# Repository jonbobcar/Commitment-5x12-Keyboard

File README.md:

# Lizard Trick 5x12 Keyboard
 A cherry mx compatible 5x12 ortholinear keyboard

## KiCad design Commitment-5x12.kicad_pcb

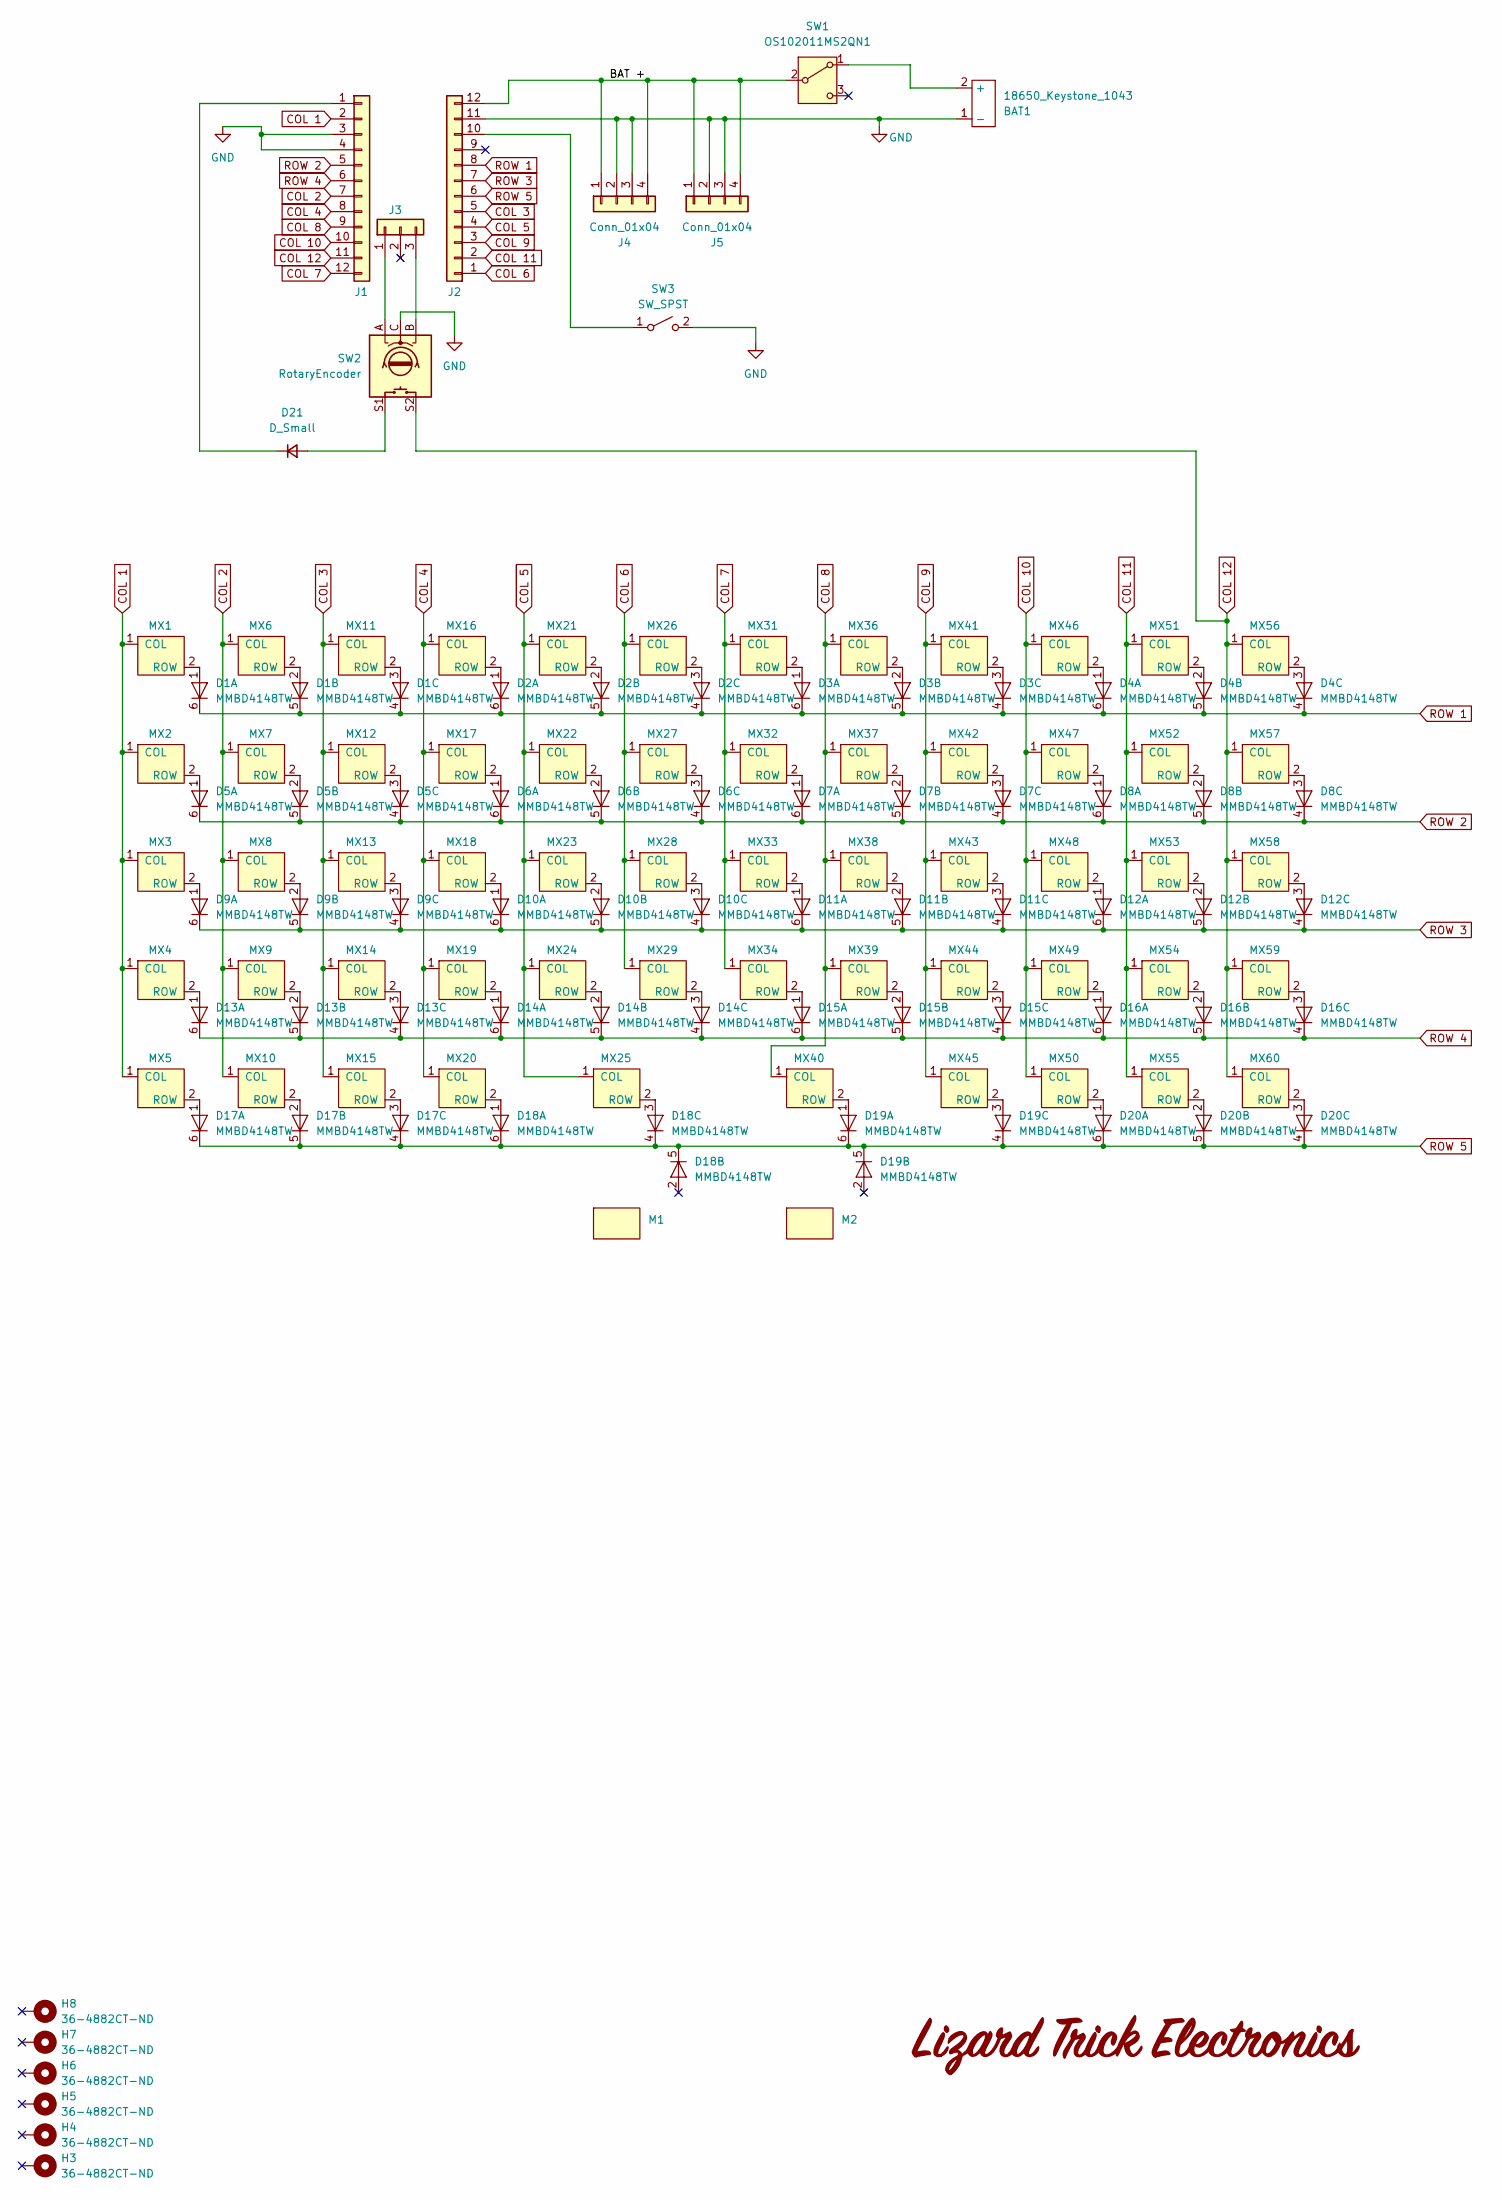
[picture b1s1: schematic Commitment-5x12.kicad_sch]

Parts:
BAT1: 18650_Keystone_1043; Keystone 1043 18650
D1, D2, D3, D4, D5, D6, D7, D8, D9, D10, D11, D12, D13, D14, D15, D16, D17, D18, D19, D20: MMBD4148TW; SOT-363_SC-70-6
D21: D_Small; D_SOD-123
H3, H4, H5, H6, H7, H8: 36-4882CT-ND; Keystone Standoff 4-40 .125
J1, J2: Conn_01x13; PinSocket_1x12_P2.54mm_Vertical
J3: Conn_01x03; PinSocket_1x03_P2.54mm_Vertical
J4, J5: Conn_01x04; MagneticHeader_1x04_P2.54mm_Vertical
M1, M2: MX_2U_Stabilizer_Mount
MX1, MX2, MX3, MX4, MX5, MX6, MX7, MX8, MX9, MX10, MX11, MX12, MX13, MX14, MX15, MX16, MX17, MX18, MX19, MX20, MX21, MX22, MX23, MX24, MX25, MX26, MX27, MX28, MX29, MX31, MX32, MX33, MX34, MX36, MX37, MX38, MX39, MX40, MX41, MX42, MX43, MX44, MX45, MX46, MX47, MX48, MX49, MX50, MX51, MX52, MX53, MX54, MX55, MX56, MX57, MX58, MX59, MX60: MX_Switch; Kailh_MX_Hotswap_Socket
SW1: OS102011MS2QN1; SW_Slide_SPDT_Straight_CK_OS102011MS2Q
SW2: RotaryEncoder; RotaryEncoder_Bourns_PEC11L
SW3: SW_SPST; Omron_B3F-1000

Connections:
/BAT +: J2.12, J4.1, J4.4, J5.1, J5.4, SW1.2 (B)
COL 1: J1.2, MX1.1 (COL), MX2.1 (COL), MX3.1 (COL), MX4.1 (COL), MX5.1 (COL)
COL 2: J1.7, MX6.1 (COL), MX7.1 (COL), MX8.1 (COL), MX9.1 (COL), MX10.1 (COL)
COL 3: J2.5, MX11.1 (COL), MX12.1 (COL), MX13.1 (COL), MX14.1 (COL), MX15.1 (COL)
COL 4: J1.8, MX16.1 (COL), MX17.1 (COL), MX18.1 (COL), MX19.1 (COL), MX20.1 (COL)
COL 5: J2.4, MX21.1 (COL), MX22.1 (COL), MX23.1 (COL), MX24.1 (COL), MX25.1 (COL)
COL 6: J2.1, MX26.1 (COL), MX27.1 (COL), MX28.1 (COL), MX29.1 (COL)
COL 7: J1.12, MX31.1 (COL), MX32.1 (COL), MX33.1 (COL), MX34.1 (COL)
COL 8: J1.9, MX36.1 (COL), MX37.1 (COL), MX38.1 (COL), MX39.1 (COL), MX40.1 (COL)
COL 9: J2.3, MX41.1 (COL), MX42.1 (COL), MX43.1 (COL), MX44.1 (COL), MX45.1 (COL)
COL 10: J1.10, MX46.1 (COL), MX47.1 (COL), MX48.1 (COL), MX49.1 (COL), MX50.1 (COL)
COL 11: J2.2, MX51.1 (COL), MX52.1 (COL), MX53.1 (COL), MX54.1 (COL), MX55.1 (COL)
COL 12: J1.11, MX56.1 (COL), MX57.1 (COL), MX58.1 (COL), MX59.1 (COL), MX60.1 (COL), SW2.S2
GND: BAT1.1 (-), J1.3, J1.4, J2.11, J4.2, J4.3, J5.2, J5.3, SW2.C, SW3.2 (B)
unnamed: BAT1.2 (+), SW1.1 (A)
unnamed: D1.1 (A), MX1.2 (ROW)
unnamed: D1.2 (A), MX6.2 (ROW)
unnamed: D1.3 (A), MX11.2 (ROW)
unnamed: D2.1 (A), MX16.2 (ROW)
unnamed: D2.2 (A), MX21.2 (ROW)
unnamed: D2.3 (A), MX26.2 (ROW)
unnamed: D3.1 (A), MX31.2 (ROW)
unnamed: D3.2 (A), MX36.2 (ROW)
unnamed: D3.3 (A), MX41.2 (ROW)
unnamed: D4.1 (A), MX46.2 (ROW)
unnamed: D4.2 (A), MX51.2 (ROW)
unnamed: D4.3 (A), MX56.2 (ROW)
unnamed: D5.1 (A), MX2.2 (ROW)
unnamed: D5.2 (A), MX7.2 (ROW)
unnamed: D5.3 (A), MX12.2 (ROW)
unnamed: D6.1 (A), MX17.2 (ROW)
unnamed: D6.2 (A), MX22.2 (ROW)
unnamed: D6.3 (A), MX27.2 (ROW)
unnamed: D7.1 (A), MX32.2 (ROW)
unnamed: D7.2 (A), MX37.2 (ROW)
unnamed: D7.3 (A), MX42.2 (ROW)
unnamed: D8.1 (A), MX47.2 (ROW)
unnamed: D8.2 (A), MX52.2 (ROW)
unnamed: D8.3 (A), MX57.2 (ROW)
unnamed: D9.1 (A), MX3.2 (ROW)
unnamed: D9.2 (A), MX8.2 (ROW)
unnamed: D9.3 (A), MX13.2 (ROW)
unnamed: D10.1 (A), MX18.2 (ROW)
unnamed: D10.2 (A), MX23.2 (ROW)
unnamed: D10.3 (A), MX28.2 (ROW)
unnamed: D11.1 (A), MX33.2 (ROW)
unnamed: D11.2 (A), MX38.2 (ROW)
unnamed: D11.3 (A), MX43.2 (ROW)
unnamed: D12.1 (A), MX48.2 (ROW)
unnamed: D12.2 (A), MX53.2 (ROW)
unnamed: D12.3 (A), MX58.2 (ROW)
unnamed: D13.1 (A), MX4.2 (ROW)
unnamed: D13.2 (A), MX9.2 (ROW)
unnamed: D13.3 (A), MX14.2 (ROW)
unnamed: D14.1 (A), MX19.2 (ROW)
unnamed: D14.2 (A), MX24.2 (ROW)
unnamed: D14.3 (A), MX29.2 (ROW)
unnamed: D15.1 (A), MX34.2 (ROW)
unnamed: D15.2 (A), MX39.2 (ROW)
unnamed: D15.3 (A), MX44.2 (ROW)
unnamed: D16.1 (A), MX49.2 (ROW)
unnamed: D16.2 (A), MX54.2 (ROW)
unnamed: D16.3 (A), MX59.2 (ROW)
unnamed: D17.1 (A), MX5.2 (ROW)
unnamed: D17.2 (A), MX10.2 (ROW)
unnamed: D17.3 (A), MX15.2 (ROW)
unnamed: D18.1 (A), MX20.2 (ROW)
unnamed: D18.3 (A), MX25.2 (ROW)
unnamed: D19.1 (A), MX40.2 (ROW)
unnamed: D19.3 (A), MX45.2 (ROW)
unnamed: D20.1 (A), MX50.2 (ROW)
unnamed: D20.2 (A), MX55.2 (ROW)
unnamed: D20.3 (A), MX60.2 (ROW)
unnamed: D21.2 (A), SW2.S1
unnamed: D21.1 (K), J1.1
unnamed: J2.10, SW3.1 (A)
unnamed: J3.1, SW2.A
unnamed: J3.3, SW2.B
ROW 1: D1.4 (K), D1.5 (K), D1.6 (K), D2.4 (K), D2.5 (K), D2.6 (K), D3.4 (K), D3.5 (K), D3.6 (K), D4.4 (K), D4.5 (K), D4.6 (K), J2.8
ROW 2: D5.4 (K), D5.5 (K), D5.6 (K), D6.4 (K), D6.5 (K), D6.6 (K), D7.4 (K), D7.5 (K), D7.6 (K), D8.4 (K), D8.5 (K), D8.6 (K), J1.5
ROW 3: D9.4 (K), D9.5 (K), D9.6 (K), D10.4 (K), D10.5 (K), D10.6 (K), D11.4 (K), D11.5 (K), D11.6 (K), D12.4 (K), D12.5 (K), D12.6 (K), J2.7
ROW 4: D13.4 (K), D13.5 (K), D13.6 (K), D14.4 (K), D14.5 (K), D14.6 (K), D15.4 (K), D15.5 (K), D15.6 (K), D16.4 (K), D16.5 (K), D16.6 (K), J1.6
ROW 5: D17.4 (K), D17.5 (K), D17.6 (K), D18.4 (K), D18.5 (K), D18.6 (K), D19.4 (K), D19.5 (K), D19.6 (K), D20.4 (K), D20.5 (K), D20.6 (K), J2.6

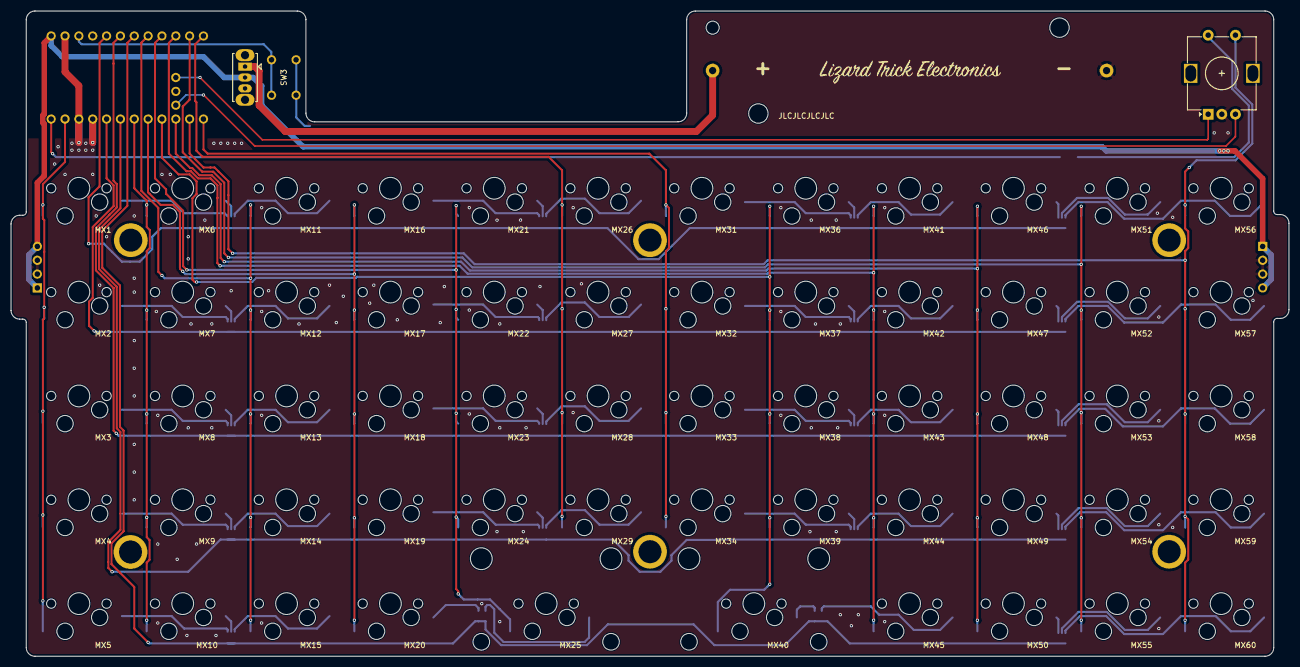
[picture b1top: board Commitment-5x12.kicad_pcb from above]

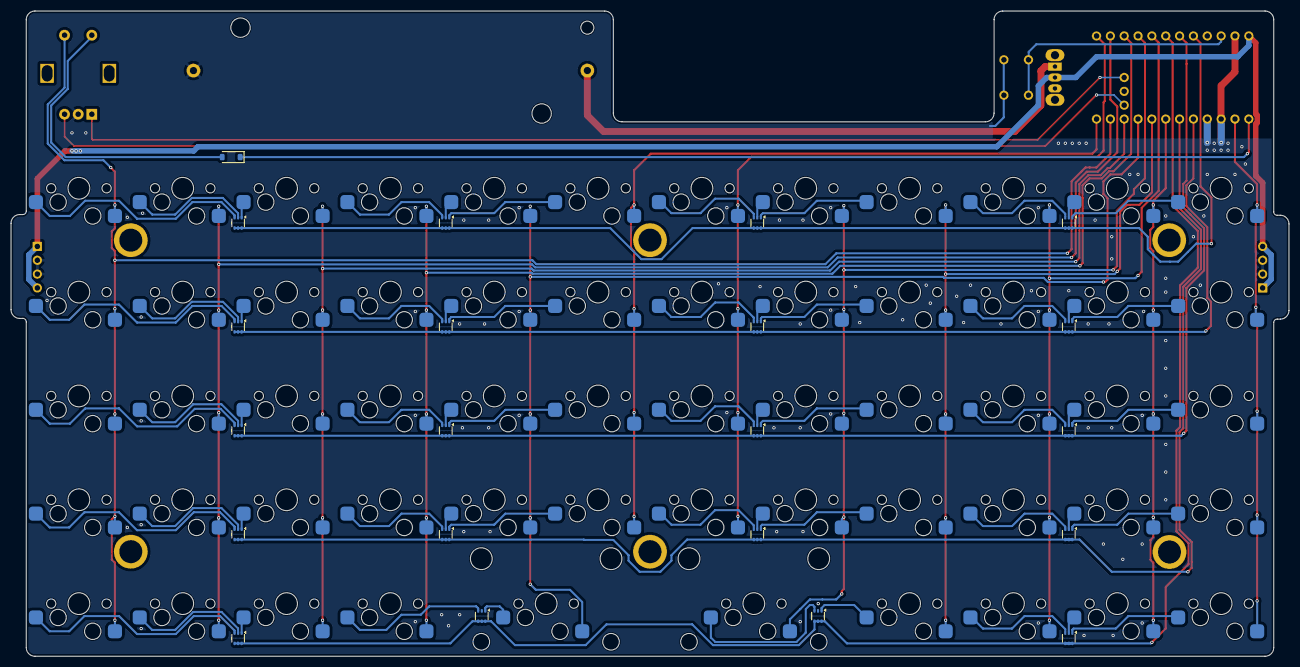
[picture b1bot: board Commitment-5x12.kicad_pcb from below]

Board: 2 copper layers, 234.4 x 118.4 mm, 96 parts (27 on the bottom side), 83 nets.

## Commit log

2025-01-01 Create revision checklist
2025-01-07 Update revision checklist
2025-01-09 Working toward revision 1
2025-01-09 working toward rev 1
2025-01-11 Create LICENSE
2025-01-12 updated footprints to include 3D cad files
2025-01-13 Switched to B3F reset switch
2025-01-13 Updated B3F 3D CAD model
2025-01-19 Disconnected encoder C from microcontroller and connected it to ground
2025-01-19 Added NC label to J3 P2
2025-01-19 Minor routing adjustment
